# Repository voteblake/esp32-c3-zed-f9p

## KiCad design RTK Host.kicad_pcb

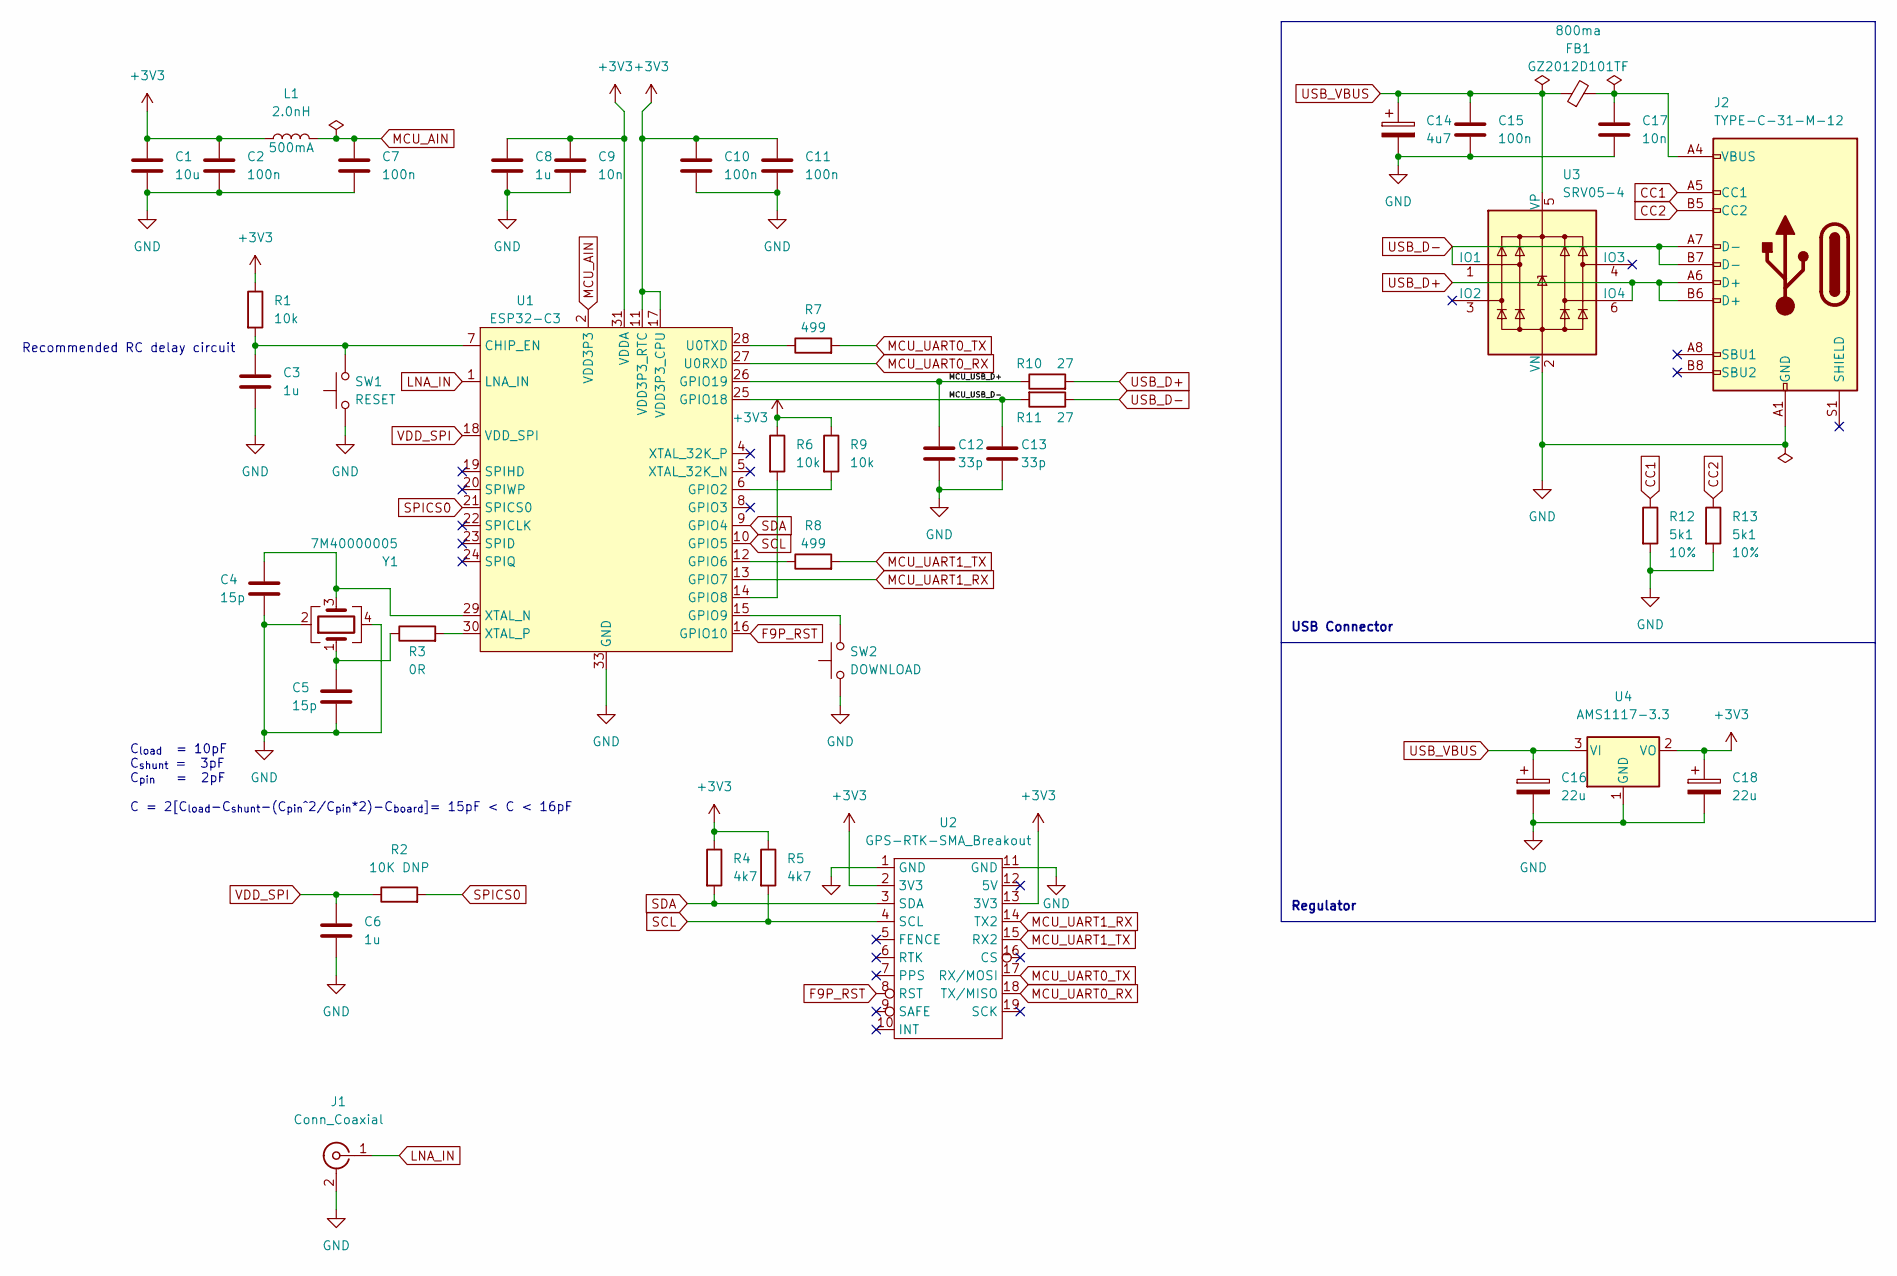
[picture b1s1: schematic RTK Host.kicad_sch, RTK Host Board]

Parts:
C1: 10u; C_0603_1608Metric
C2, C7, C10, C11, C15: 100n; C_0402_1005Metric
C3, C6, C8: 1u; C_0603_1608Metric
C4, C5: 15p; C_0402_1005Metric
C9, C17: 10n; C_0402_1005Metric
C12, C13: 33p; C_0402_1005Metric
C14: 4u7; CP_EIA-3216-18_Kemet-A
C16, C18: 22u; CP_EIA-3216-18_Kemet-A; JLCPCB Part # C11366
FB1: GZ2012D101TF; L_0805_2012Metric; Rating 800ma
J1: Conn_Coaxial; SMA_Amphenol_901-144_Vertical
J2: TYPE-C-31-M-12; USB_C_Receptacle_HRO_TYPE-C-31-M-12; JLCPCB Part # C165948
L1: 2.0nH; L_0402_1005Metric; JLCPCB Part # C98758
R1, R6, R9: 10k; R_0603_1608Metric
R2: 10K DNP; R_1206_3216Metric_Pad1.30x1.75mm_HandSolder
R3: 0R; R_0402_1005Metric_Pad0.72x0.64mm_HandSolder
R4, R5: 4k7; R_0603_1608Metric
R7, R8: 499; R_0805_2012Metric
R10, R11: 27; R_0805_2012Metric
R12, R13: 5k1; R_0603_1608Metric; Tolerance 10%
SW1: RESET; SW_SPST_TL3342
SW2: DOWNLOAD; SW_SPST_TL3342
U1: ESP32-C3; QFN-32-1EP_5x5mm_P0.5mm_EP3.7x3.7mm
U2: GPS-RTK-SMA_Breakout; GPS-RTK-SMA Breakout
U3: SRV05-4; SOT-23-6
U4: AMS1117-3.3; SOT-223-3_TabPin2
Y1: 7M40000005; Crystal_SMD_TXC_7M-4Pin_3.2x2.5mm; JLCPCB Part # C90924

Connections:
+3V3: C1.1, C2.1, C8.1, C9.1, C10.1, C11.1, C18.1, L1.1, R1.1, R4.1, R5.1, R6.1, R9.1, U1.11 (VDD3P3_RTC), U1.17 (VDD3P3_CPU), U1.31 (VDDA), U1.32 (VDDA), U2.2 (3V3), U2.13 (3V3), U4.2 (VO)
/MCU_USB_D+: C12.1, R10.1, U1.26 (GPIO19)
/MCU_USB_D-: C13.1, R11.2, U1.25 (GPIO18)
CC1: J2.A5 (CC1), R12.1
CC2: J2.B5 (CC2), R13.1
F9P_RST: U1.16 (GPIO10), U2.8 (RST)
GND: C1.2, C2.2, C3.2, C4.2, C5.2, C6.2, C7.2, C8.2, C9.2, C10.2, C11.2, C12.2, C13.2, C14.2, C15.2, C16.2, C17.2, C18.2, J1.2 (Ext), J2.A1 (GND), J2.A12 (GND), J2.B1 (GND), J2.B12 (GND), R12.2, R13.2, SW1.1, SW2.1, U1.33 (GND), U2.1 (GND), U2.11 (GND), U3.2 (VN), U4.1 (GND), Y1.2, Y1.4; also elsewhere on the board
LNA_IN: J1.1 (In), U1.1 (LNA_IN)
MCU_AIN: C7.1, L1.2, U1.2 (VDD3P3), U1.3 (VDD3P3)
MCU_UART0_RX: U1.27 (U0RXD), U2.18 (TX/MISO)
MCU_UART0_TX: R7.2, U2.17 (RX/MOSI)
MCU_UART1_RX: U1.13 (GPIO7), U2.14 (TX2)
MCU_UART1_TX: R8.2, U2.15 (RX2)
unnamed: C3.1, R1.2, SW1.2, U1.7 (CHIP_EN)
unnamed: C4.1, U1.29 (XTAL_N), Y1.3
unnamed: C5.1, R3.1, Y1.1
unnamed: C17.1, FB1.2, J2.A4 (VBUS), J2.A9 (VBUS), J2.B4 (VBUS), J2.B9 (VBUS)
unnamed: R3.2, U1.30 (XTAL_P)
unnamed: R6.2, U1.14 (GPIO8)
unnamed: R7.1, U1.28 (U0TXD)
unnamed: R8.1, U1.12 (GPIO6)
unnamed: R9.2, U1.6 (GPIO2)
unnamed: SW2.2, U1.15 (GPIO9)
SCL: R5.2, U1.10 (GPIO5), U2.4 (SCL)
SDA: R4.2, U1.9 (GPIO4), U2.3 (SDA)
SPICS0: R2.2, U1.21 (SPICS0)
USB_D+: J2.A6 (D+), J2.B6 (D+), R10.2, U3.6 (IO4)
USB_D-: J2.A7 (D-), J2.B7 (D-), R11.1, U3.1 (IO1)
USB_VBUS: C14.1, C15.1, C16.1, FB1.1, U3.5 (VP), U4.3 (VI); also elsewhere on the board
VDD_SPI: C6.1, R2.1, U1.18 (VDD_SPI)

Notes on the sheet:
Recommended RC delay circuit
Regulator
USB Connector
C_{load} = 10pF C_{shunt} = 3pF C_{pin} = 2pF C = 2[C_{load}-C_{shunt}-(C_{pin}^2/C_{pin}*2)-C_{board}]= 15pF < C < 16pF

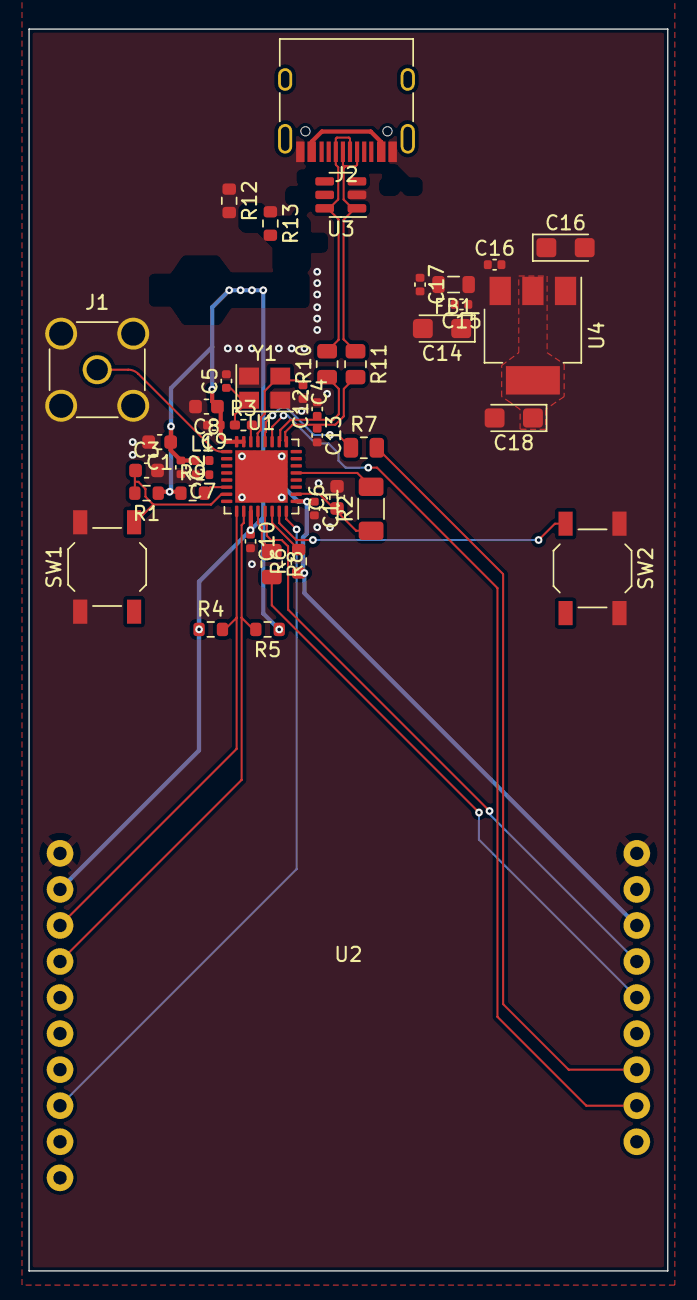
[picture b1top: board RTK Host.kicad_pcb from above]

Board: 4 copper layers, 45.0 x 87.5 mm, 43 parts (0 on the bottom side), 30 nets.

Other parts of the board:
C16#2: 10n; C_0402_1005Metric

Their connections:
GND: C16#2.2; also elsewhere on the board
USB_VBUS: C16#2.1; also elsewhere on the board

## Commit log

2022-08-16 Initial Check In
    Schematic roughly feature complete, PCB needs final tuning of power module placement and power routing.
2022-08-16 License repository as CERN-OHL-P-2.0
